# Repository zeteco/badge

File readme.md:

# ZeTeCo-Badge

These are the PCB-Files ([KiCad](https://www.kicad.org/)) of the Badge for the [ZeTeCo-Camp](https://zeteco.ch/). The original design was made by [@bluetonyum](https://github.com/bluetonyum).

Please also visit the [Wiki-Page](https://wiki.zeteco.ch/wiki/Badge)

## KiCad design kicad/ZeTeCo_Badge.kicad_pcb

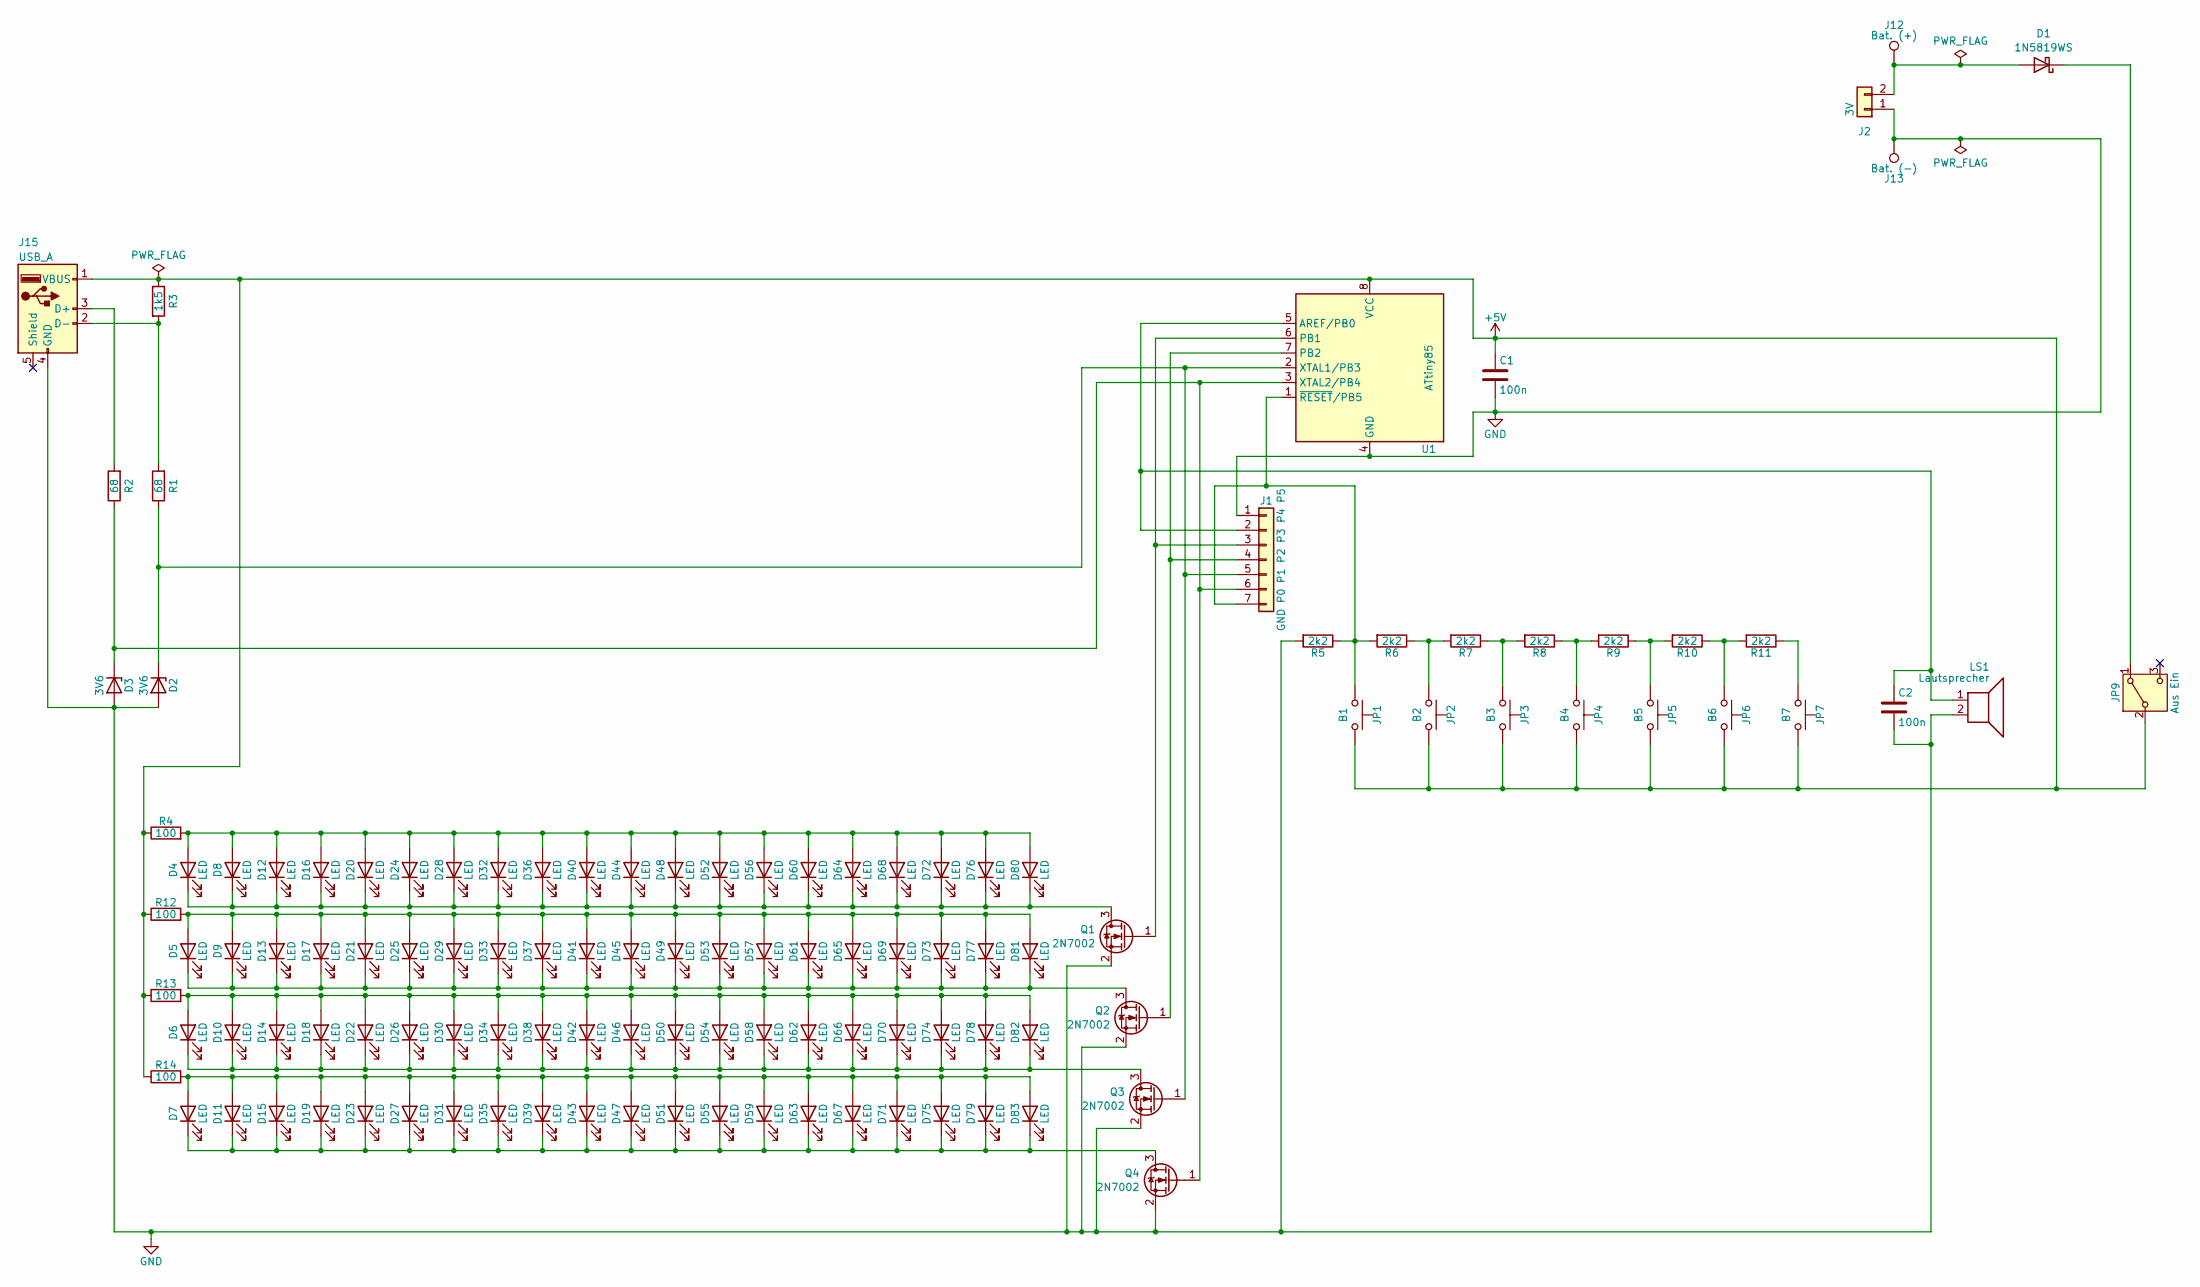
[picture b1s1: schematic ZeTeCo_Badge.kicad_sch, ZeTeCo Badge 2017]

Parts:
C1, C2: 100n; C_1206_3216Metric_Pad1.33x1.80mm_HandSolder
D1: 1N5819WS; D_1206_3216Metric_Pad1.42x1.75mm_HandSolder
D2, D3: 3V6; D_1206_3216Metric_Pad1.42x1.75mm_HandSolder
D4, D5, D6, D7, D8, D9, D10, D11, D12, D13, D14, D15, D16, D17, D18, D19, D20, D21, D22, D23, D24, D25, D26, D27, D28, D29, D30, D31, D32, D33, D34, D35, D36, D37, D38, D39, D40, D41, D42, D43, D44, D45, D46, D47, D48, D49, D50, D51, D52, D53, D54, D55, D56, D57, D58, D59, D60, D61, D62, D63, D64, D65, D66, D67, D68, D69, D70, D71, D72, D73, D74, D75, D76, D77, D78, D79, D80, D81, D82, D83: LED; LED_1206_3216Metric_Pad1.42x1.75mm_HandSolder
J1: GND P0 P1 P2 P3 P4 P5; PinHeader_1x07_P2.54mm_Vertical
J2: 3V; PinHeader_1x02_P2.54mm_Vertical
J12: Bat. (+); TestPoint_Keystone_5000-5004_Miniature
J13: Bat. (-); TestPoint_Keystone_5000-5004_Miniature
J15: USB_A; usb-PCB
JP1: B1; SW_SPST_TL3342
JP2: B2; SW_SPST_TL3342
JP3: B3; SW_SPST_TL3342
JP4: B4; SW_SPST_TL3342
JP5: B5; SW_SPST_TL3342
JP6: B6; SW_SPST_TL3342
JP7: B7; SW_SPST_TL3342
JP9: Aus Ein; SW_SPDT_PCM12
LS1: Lautsprecher; PinHeader_1x02_P2.54mm_Vertical
Q1, Q2, Q3, Q4: 2N7002; SOT-23
R1, R2: 68; R_1206_3216Metric_Pad1.30x1.75mm_HandSolder
R3: 1k5; R_1206_3216Metric_Pad1.30x1.75mm_HandSolder
R4, R12, R13, R14: 100; R_1206_3216Metric_Pad1.30x1.75mm_HandSolder
R5, R6, R7, R8, R9, R10, R11: 2k2; R_1206_3216Metric_Pad1.30x1.75mm_HandSolder
U1: ATtiny85; SOIC-8W_5.3x5.3mm_P1.27mm

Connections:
+5V: C1.1, J15.1 (VBUS), JP1.2, JP2.2, JP3.2, JP4.2, JP5.2, JP6.2, JP7.2, JP9.2 (B), R3.1, R4.1, R12.1, R13.1, R14.1, U1.8 (VCC)
GND: C1.2, C2.2, D2.2 (A), D3.2 (A), J1.1, J2.1, J13.1, J15.4 (GND), LS1.2, Q1.2 (S), Q2.2 (S), Q3.2 (S), Q4.2 (S), R5.2, U1.4 (GND)
unnamed: D1.2 (A), J2.2, J12.1
unnamed: D1.1 (K), JP9.1 (A)
unnamed: D2.1 (K), J1.5, Q3.1 (G), R1.1, U1.2 (XTAL1/PB3)
unnamed: D3.1 (K), J1.6, Q4.1 (G), R2.1, U1.3 (XTAL2/PB4)
unnamed: D6.2 (A), D10.2 (A), D14.2 (A), D18.2 (A), D22.2 (A), D26.2 (A), D30.2 (A), D34.2 (A), D38.2 (A), D42.2 (A), D46.2 (A), D50.2 (A), D54.2 (A), D58.2 (A), D62.2 (A), D66.2 (A), D70.2 (A), D74.2 (A), D78.2 (A), D82.2 (A), R13.2
unnamed: D6.1 (K), D10.1 (K), D14.1 (K), D18.1 (K), D22.1 (K), D26.1 (K), D30.1 (K), D34.1 (K), D38.1 (K), D42.1 (K), D46.1 (K), D50.1 (K), D54.1 (K), D58.1 (K), D62.1 (K), D66.1 (K), D70.1 (K), D74.1 (K), D78.1 (K), D82.1 (K), Q3.3 (D)
unnamed: D7.2 (A), D11.2 (A), D15.2 (A), D19.2 (A), D23.2 (A), D27.2 (A), D31.2 (A), D35.2 (A), D39.2 (A), D43.2 (A), D47.2 (A), D51.2 (A), D55.2 (A), D59.2 (A), D63.2 (A), D67.2 (A), D71.2 (A), D75.2 (A), D79.2 (A), D83.2 (A), R14.2
unnamed: D7.1 (K), D11.1 (K), D15.1 (K), D19.1 (K), D23.1 (K), D27.1 (K), D31.1 (K), D35.1 (K), D39.1 (K), D43.1 (K), D47.1 (K), D51.1 (K), D55.1 (K), D59.1 (K), D63.1 (K), D67.1 (K), D71.1 (K), D75.1 (K), D79.1 (K), D83.1 (K), Q4.3 (D)
unnamed: D4.2 (A), D8.2 (A), D12.2 (A), D16.2 (A), D20.2 (A), D24.2 (A), D28.2 (A), D32.2 (A), D36.2 (A), D40.2 (A), D44.2 (A), D48.2 (A), D52.2 (A), D56.2 (A), D60.2 (A), D64.2 (A), D68.2 (A), D72.2 (A), D76.2 (A), D80.2 (A), R4.2
unnamed: D4.1 (K), D8.1 (K), D12.1 (K), D16.1 (K), D20.1 (K), D24.1 (K), D28.1 (K), D32.1 (K), D36.1 (K), D40.1 (K), D44.1 (K), D48.1 (K), D52.1 (K), D56.1 (K), D60.1 (K), D64.1 (K), D68.1 (K), D72.1 (K), D76.1 (K), D80.1 (K), Q1.3 (D)
unnamed: D5.2 (A), D9.2 (A), D13.2 (A), D17.2 (A), D21.2 (A), D25.2 (A), D29.2 (A), D33.2 (A), D37.2 (A), D41.2 (A), D45.2 (A), D49.2 (A), D53.2 (A), D57.2 (A), D61.2 (A), D65.2 (A), D69.2 (A), D73.2 (A), D77.2 (A), D81.2 (A), R12.2
unnamed: D5.1 (K), D9.1 (K), D13.1 (K), D17.1 (K), D21.1 (K), D25.1 (K), D29.1 (K), D33.1 (K), D37.1 (K), D41.1 (K), D45.1 (K), D49.1 (K), D53.1 (K), D57.1 (K), D61.1 (K), D65.1 (K), D69.1 (K), D73.1 (K), D77.1 (K), D81.1 (K), Q2.3 (D)
unnamed: C2.1, J1.2, LS1.1, U1.5 (AREF/PB0)
unnamed: J1.3, Q1.1 (G), U1.6 (PB1)
unnamed: J1.4, Q2.1 (G), U1.7 (PB2)
unnamed: J1.7, JP1.1, R5.1, R6.2, U1.1 (~RESET/PB5)
unnamed: J15.3 (D+), R2.2
unnamed: J15.2 (D-), R1.2, R3.2
unnamed: JP2.1, R6.1, R7.2
unnamed: JP3.1, R7.1, R8.2
unnamed: JP4.1, R8.1, R9.2
unnamed: JP5.1, R9.1, R10.2
unnamed: JP6.1, R10.1, R11.2
unnamed: JP7.1, R11.1

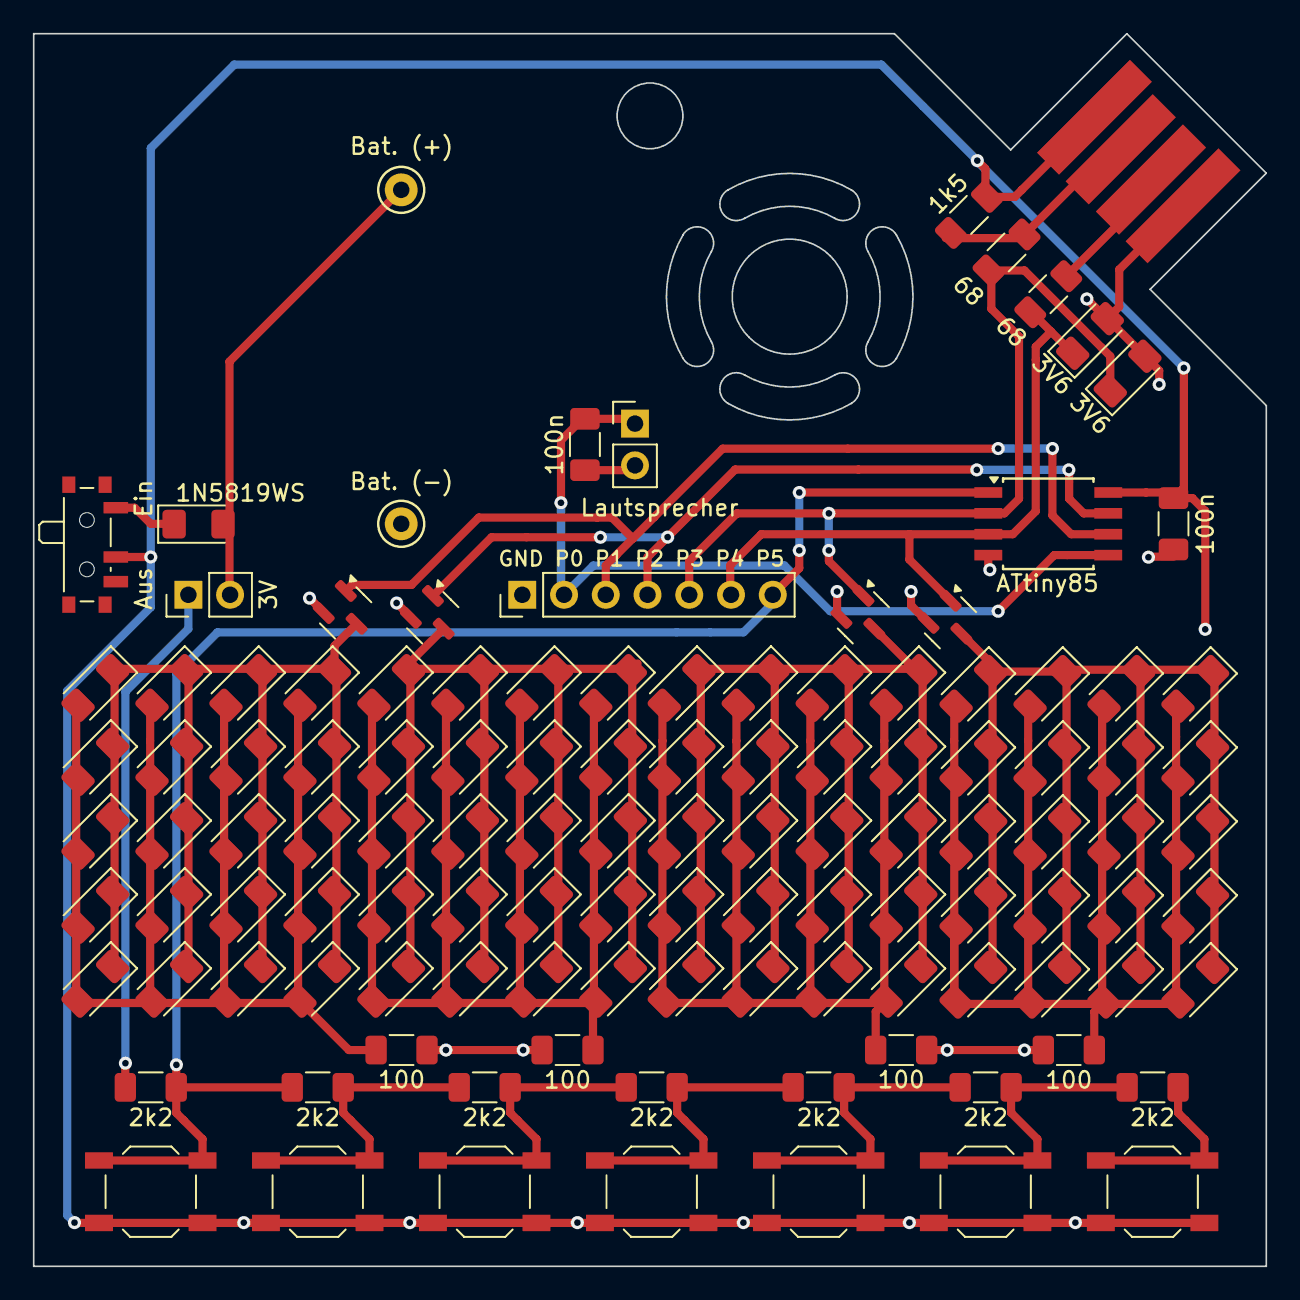
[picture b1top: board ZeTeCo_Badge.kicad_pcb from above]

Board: 2 copper layers, 75.0 x 75.0 mm, 118 parts (0 on the bottom side), 26 nets.

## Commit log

2017-09-28 MOD: initial commit
2017-09-28 ADD: Source
2024-11-05 Fix permissions
2024-11-06 Clean up backup and manufacturing files
2024-11-06 Update, cleanup and redesign PCB, add MOSFETs
2024-11-07 Replace PCB text with component values on silkscreen
2024-11-10 MOD: update readme
